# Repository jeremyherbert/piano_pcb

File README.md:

A piano PCB originally designed for use in ENGG2800 at The University of Queensland. Please see `schematic.pdf` for a schematic of the board.

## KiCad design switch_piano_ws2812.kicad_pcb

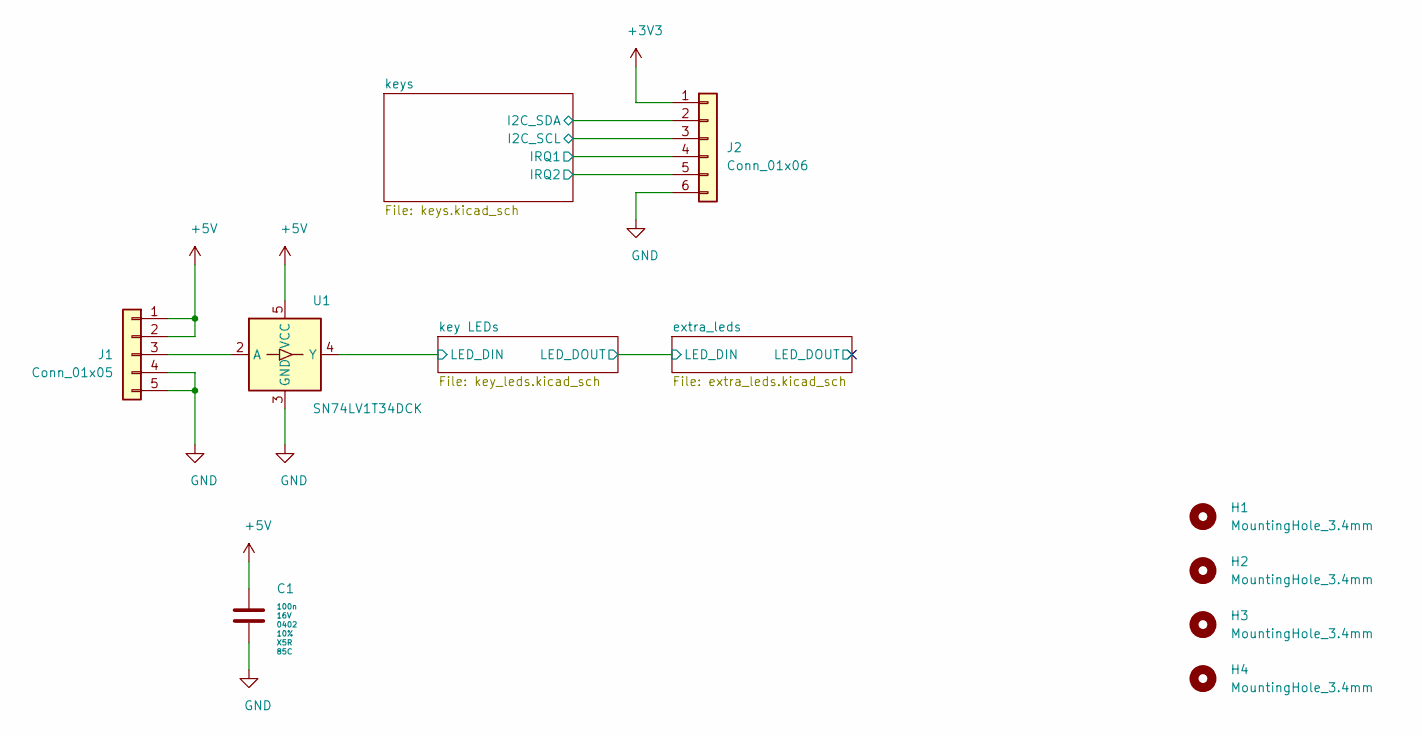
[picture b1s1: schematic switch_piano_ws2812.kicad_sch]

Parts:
C1: C,100n,16V,0402,10%,X5R,85C; C_0402_1005Metric; MFG PN CL05A104KO5NNNC; Digikey 1276-1234-1-ND
H1, H2, H3, H4: MountingHole_3.4mm
J1: Conn_01x05; Molex_KK-254_AE-6410-05A_1x05_P2.54mm_Vertical
J2: Conn_01x06; Molex_KK-254_AE-6410-06A_1x06_P2.54mm_Vertical
U1: SN74LV1T34DCK; SOT-353_SC-70-5

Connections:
+3V3: J2.1; also elsewhere on the board
+5V: C1.1, J1.1, J1.2, U1.5 (VCC); also elsewhere on the board
/I2C_SCL: J2.3; also elsewhere on the board
/IRQ1: J2.4; also elsewhere on the board
/IRQ2: J2.5; also elsewhere on the board
/LED_DIN: U1.4 (Y); also elsewhere on the board
/keys/I2C_SDA_1: J2.2; also elsewhere on the board
unnamed: J1.3, U1.2 (A)

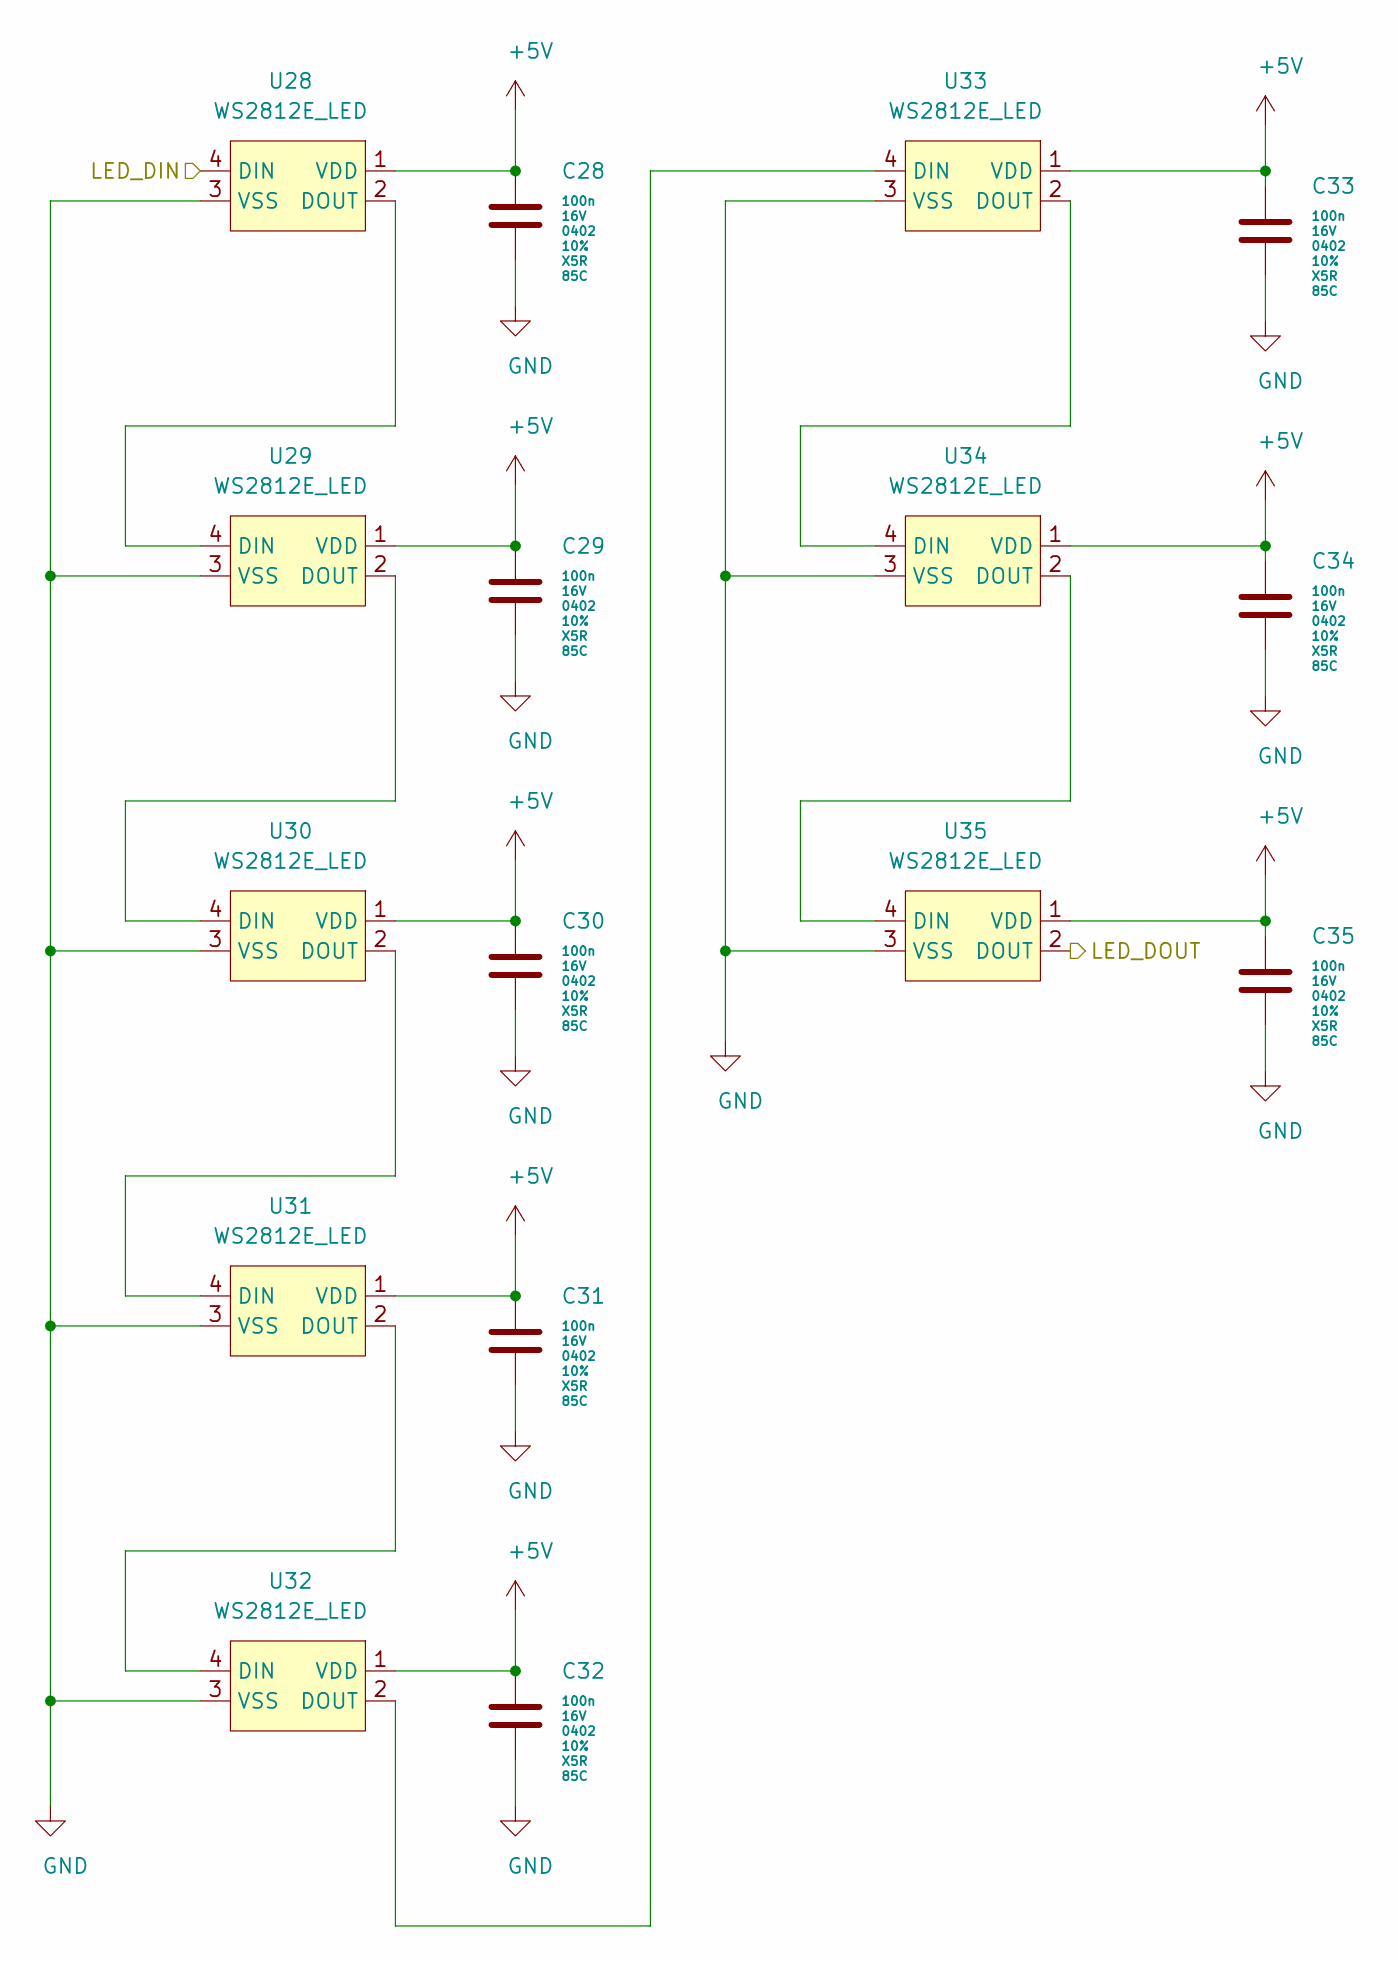
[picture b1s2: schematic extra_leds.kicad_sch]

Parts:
C28, C29, C30, C31, C32, C33, C34, C35: C,100n,16V,0402,10%,X5R,85C; C_0402_1005Metric; MFG PN CL05A104KO5NNNC; Digikey 1276-1234-1-ND
U28, U29, U30, U31, U32, U33, U34, U35: WS2812E_LED; LED_WS2812B_PLCC4_5.0x5.0mm_P3.2mm; MFG PN WS2812E; LCSC C139127

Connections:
+5V: C28.2, C29.2, C30.2, C31.2, C32.2, C33.2, C34.2, C35.2, U28.1 (VDD), U29.1 (VDD), U30.1 (VDD), U31.1 (VDD), U32.1 (VDD), U33.1 (VDD), U34.1 (VDD), U35.1 (VDD); also elsewhere on the board
/LED_DOUT: U35.2 (DOUT)
/LED_DOUT_1: U28.4 (DIN); also elsewhere on the board
unnamed: U28.2 (DOUT), U29.4 (DIN)
unnamed: U29.2 (DOUT), U30.4 (DIN)
unnamed: U30.2 (DOUT), U31.4 (DIN)
unnamed: U31.2 (DOUT), U32.4 (DIN)
unnamed: U32.2 (DOUT), U33.4 (DIN)
unnamed: U33.2 (DOUT), U34.4 (DIN)
unnamed: U34.2 (DOUT), U35.4 (DIN)

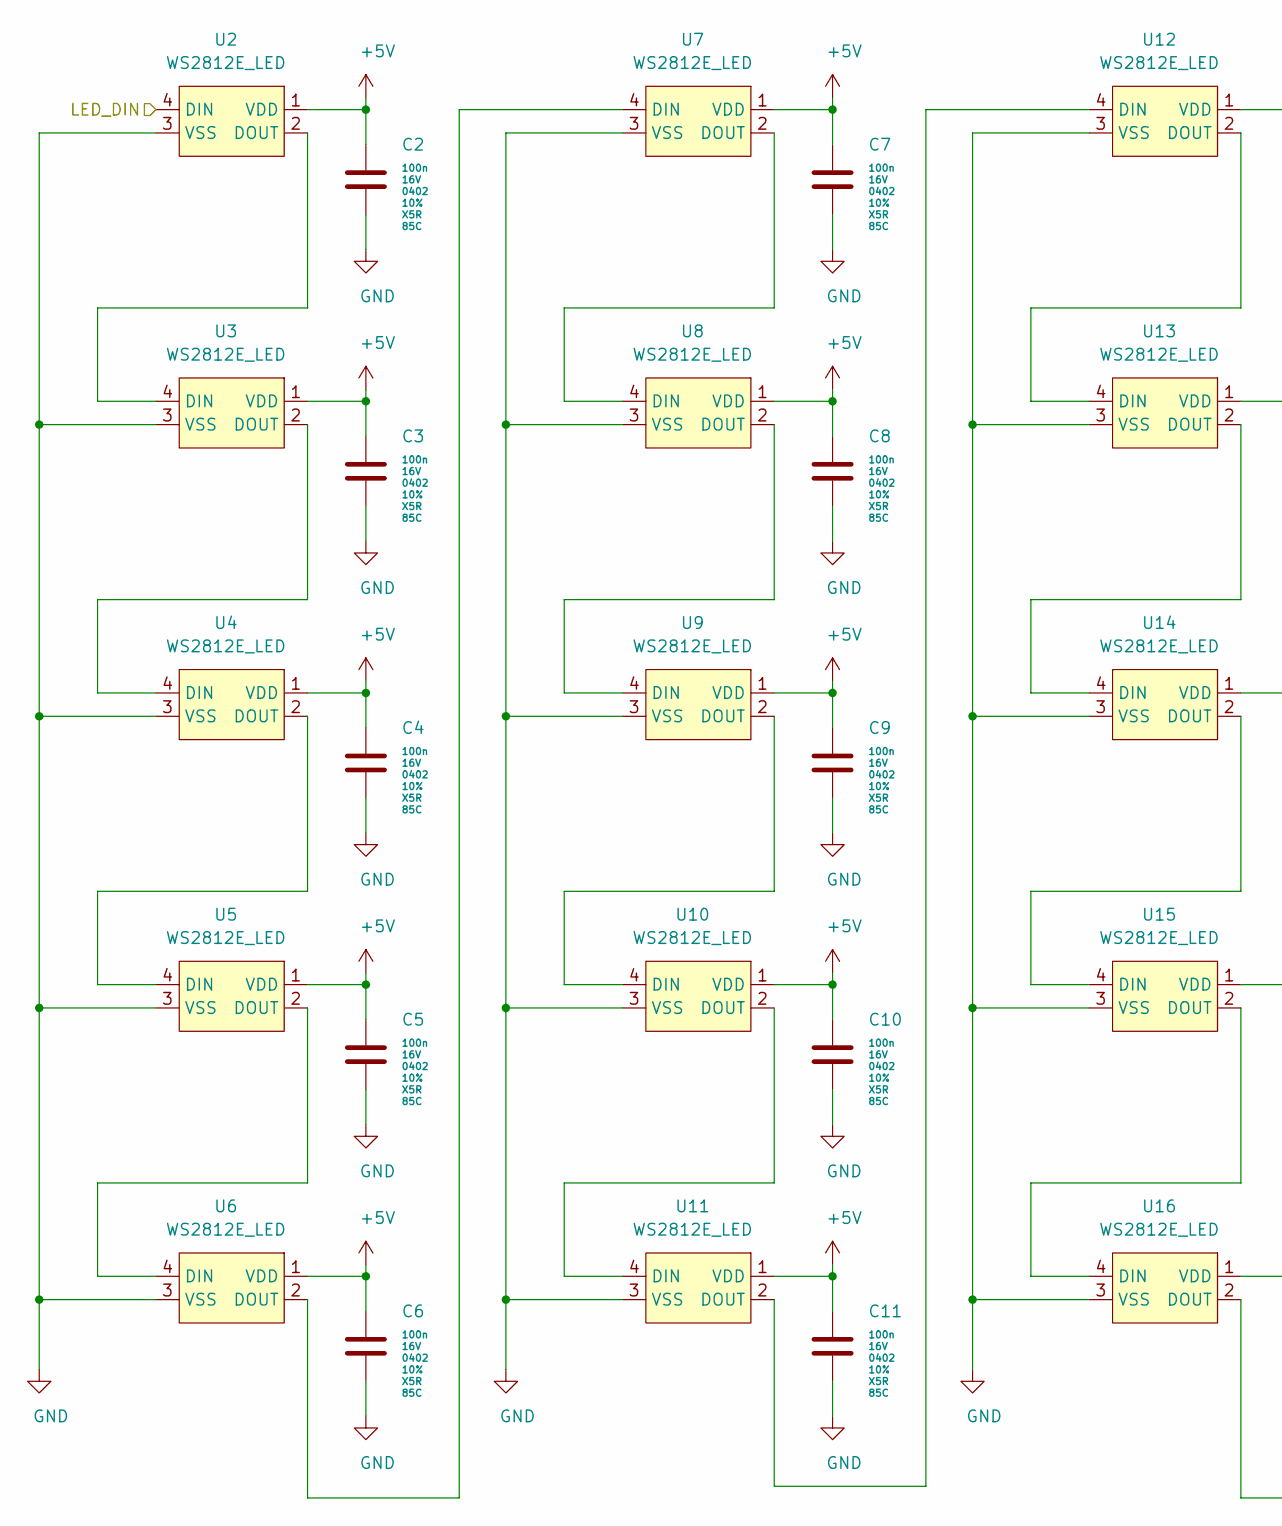
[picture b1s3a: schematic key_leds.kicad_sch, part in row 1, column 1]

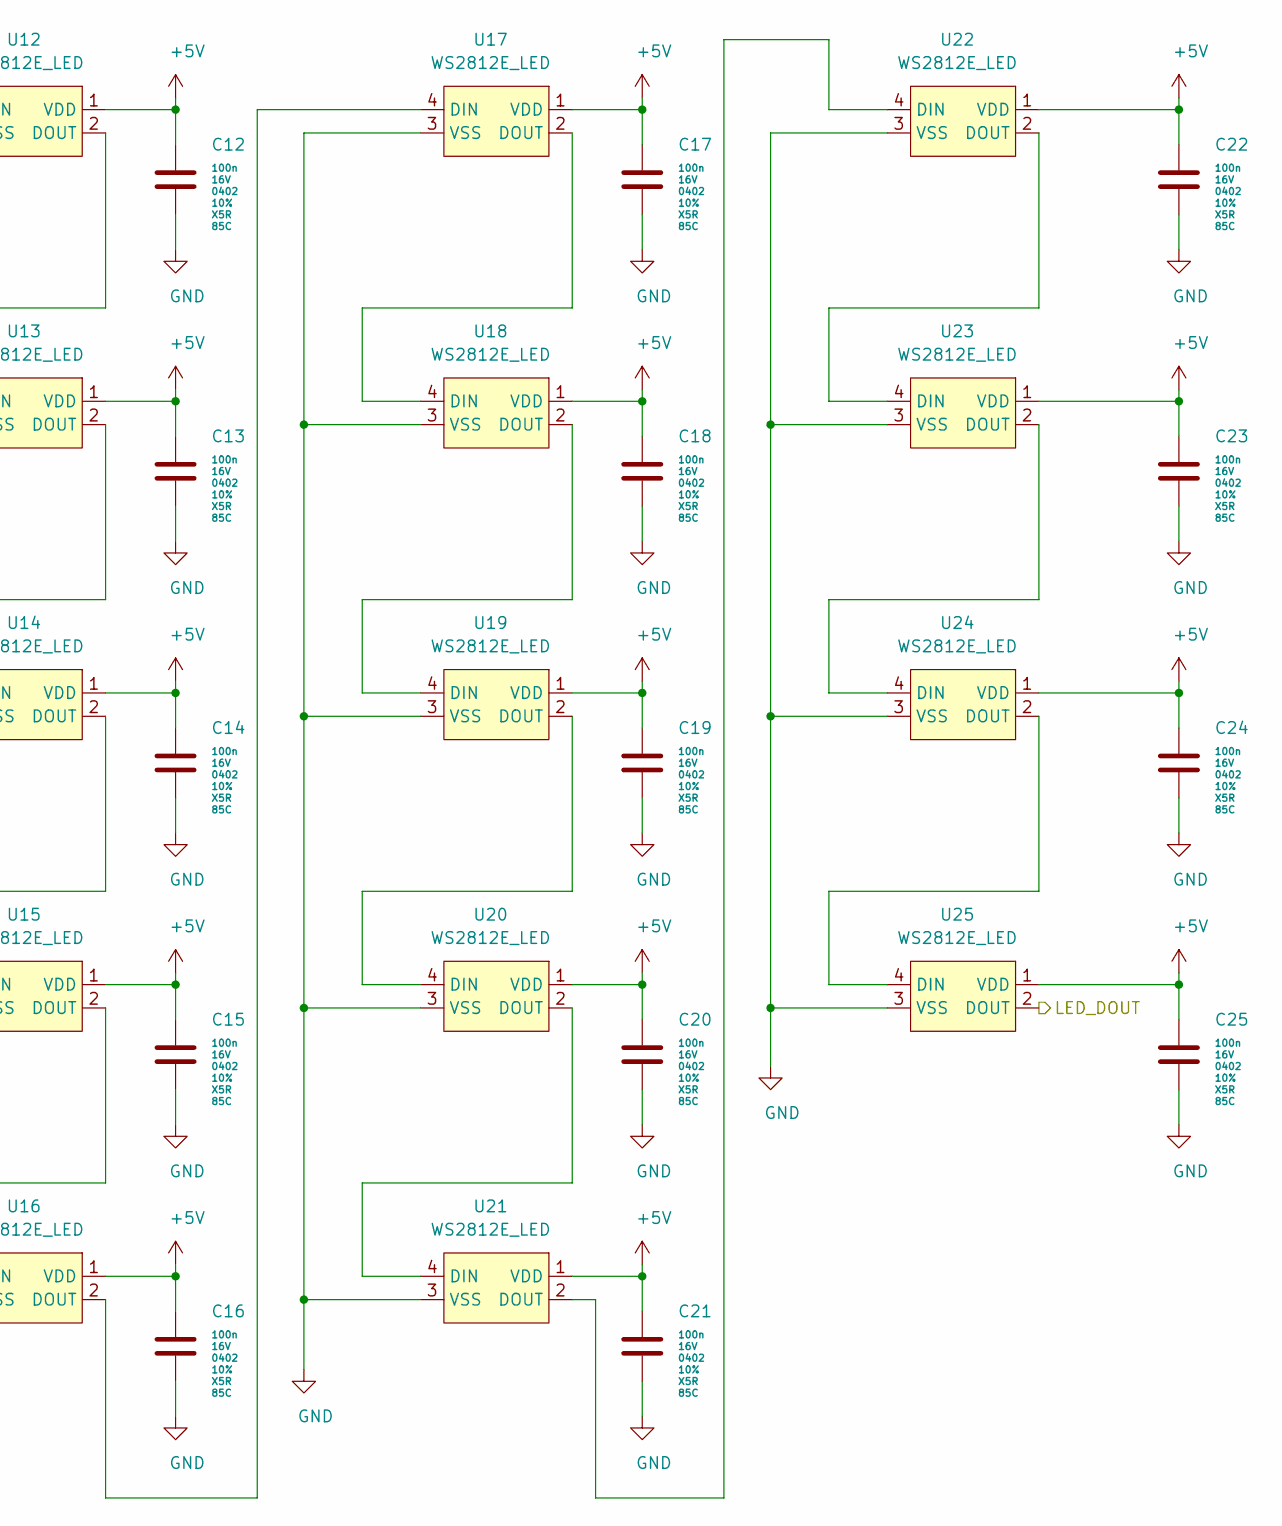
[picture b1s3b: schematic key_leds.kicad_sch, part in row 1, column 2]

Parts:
C2, C3, C4, C5, C6, C7, C8, C9, C10, C11, C12, C13, C14, C15, C16, C17, C18, C19, C20, C21, C22, C23, C24, C25: C,100n,16V,0402,10%,X5R,85C; C_0402_1005Metric; MFG PN CL05A104KO5NNNC; Digikey 1276-1234-1-ND
U2, U3, U4, U5, U6, U7, U8, U9, U10, U11, U12, U13, U14, U15, U16, U17, U18, U19, U20, U21, U22, U23, U24, U25: WS2812E_LED; LED_WS2812B_PLCC4_5.0x5.0mm_P3.2mm; MFG PN WS2812E; LCSC C139127

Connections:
+5V: C2.2, C3.2, C4.2, C5.2, C6.2, C7.2, C8.2, C9.2, C10.2, C11.2, C12.2, C13.2, C14.2, C15.2, C16.2, C17.2, C18.2, C19.2, C20.2, C21.2, C22.2, C23.2, C24.2, C25.2, U2.1 (VDD), U3.1 (VDD), U4.1 (VDD), U5.1 (VDD), U6.1 (VDD), U7.1 (VDD), U8.1 (VDD), U9.1 (VDD), U10.1 (VDD), U11.1 (VDD), U12.1 (VDD), U13.1 (VDD), U14.1 (VDD), U15.1 (VDD), U16.1 (VDD), U17.1 (VDD), U18.1 (VDD), U19.1 (VDD), U20.1 (VDD), U21.1 (VDD), U22.1 (VDD), U23.1 (VDD), U24.1 (VDD), U25.1 (VDD); also elsewhere on the board
/LED_DIN: U2.4 (DIN); also elsewhere on the board
/LED_DOUT_1: U25.2 (DOUT); also elsewhere on the board
unnamed: U2.2 (DOUT), U3.4 (DIN)
unnamed: U3.2 (DOUT), U4.4 (DIN)
unnamed: U4.2 (DOUT), U5.4 (DIN)
unnamed: U5.2 (DOUT), U6.4 (DIN)
unnamed: U6.2 (DOUT), U7.4 (DIN)
unnamed: U7.2 (DOUT), U8.4 (DIN)
unnamed: U8.2 (DOUT), U9.4 (DIN)
unnamed: U10.2 (DOUT), U11.4 (DIN)
unnamed: U9.2 (DOUT), U10.4 (DIN)
unnamed: U11.2 (DOUT), U12.4 (DIN)
unnamed: U12.2 (DOUT), U13.4 (DIN)
unnamed: U13.2 (DOUT), U14.4 (DIN)
unnamed: U14.2 (DOUT), U15.4 (DIN)
unnamed: U15.2 (DOUT), U16.4 (DIN)
unnamed: U17.2 (DOUT), U18.4 (DIN)
unnamed: U16.2 (DOUT), U17.4 (DIN)
unnamed: U18.2 (DOUT), U19.4 (DIN)
unnamed: U19.2 (DOUT), U20.4 (DIN)
unnamed: U20.2 (DOUT), U21.4 (DIN)
unnamed: U22.2 (DOUT), U23.4 (DIN)
unnamed: U21.2 (DOUT), U22.4 (DIN)
unnamed: U23.2 (DOUT), U24.4 (DIN)
unnamed: U24.2 (DOUT), U25.4 (DIN)

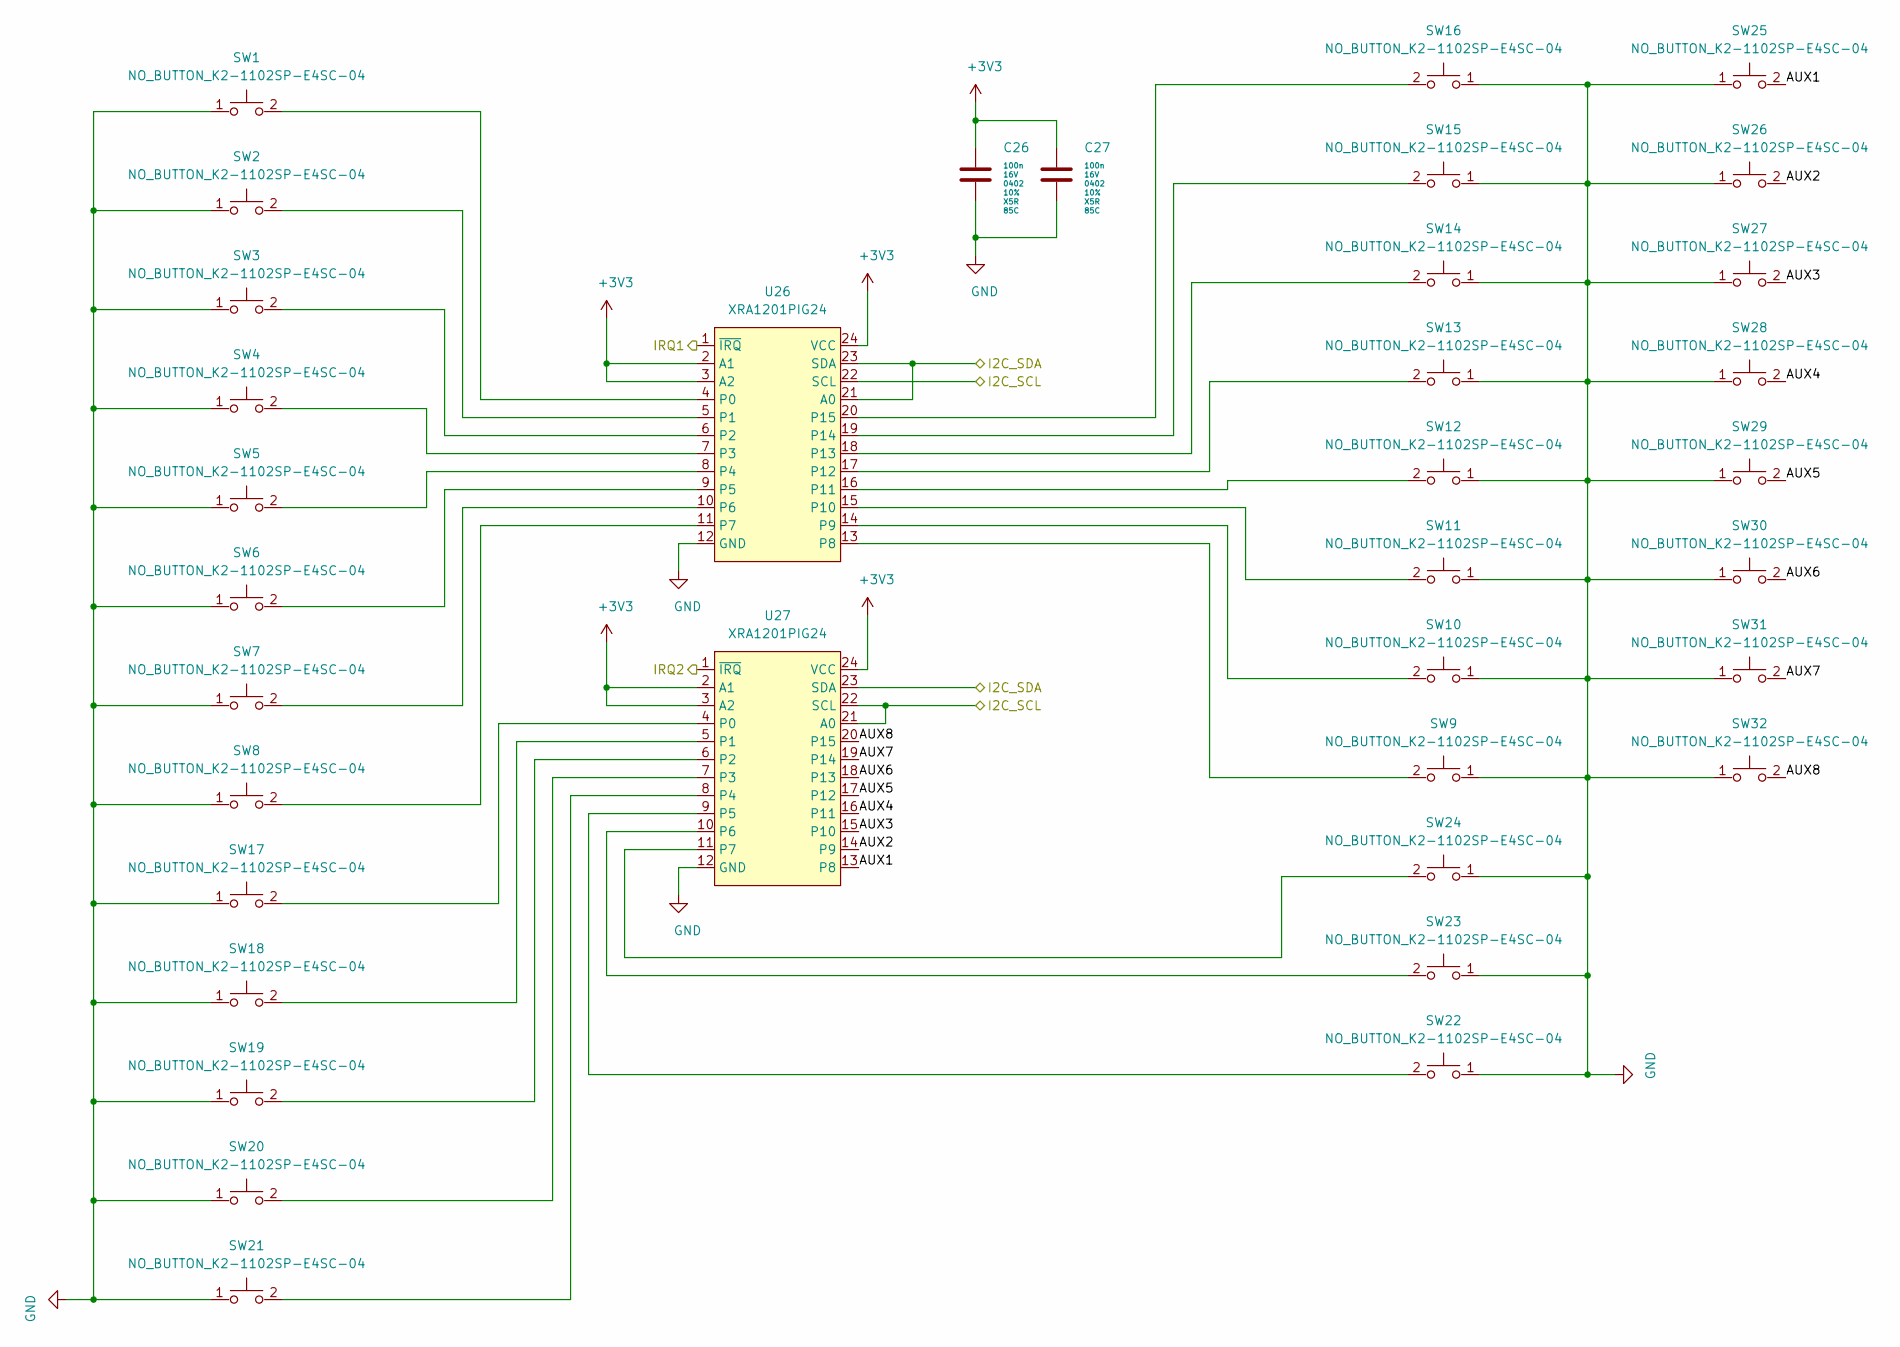
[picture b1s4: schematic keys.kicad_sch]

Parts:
C26, C27: C,100n,16V,0402,10%,X5R,85C; C_0402_1005Metric; MFG PN CL05A104KO5NNNC; Digikey 1276-1234-1-ND
SW1, SW2, SW3, SW4, SW5, SW6, SW7, SW8, SW9, SW10, SW11, SW12, SW13, SW14, SW15, SW16, SW17, SW18, SW19, SW20, SW21, SW22, SW23, SW24, SW25, SW26, SW27, SW28, SW29, SW30, SW31, SW32: NO_BUTTON_K2-1102SP-E4SC-04; SW_SPST_PTS645; MFG PN K2-1102SP-E4SC-04; LCSC C136669
U26, U27: XRA1201PIG24; TSSOP-24_4.4x7.8mm_P0.65mm; MFG PN XRA1201PIG24; Digikey XRA1201PIG24TR-F-ND

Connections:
+3V3: C26.1, C27.1, U26.2 (A1), U26.3 (A2), U26.24 (VCC), U27.2 (A1), U27.3 (A2), U27.24 (VCC); also elsewhere on the board
/I2C_SCL: U26.22 (SCL), U27.21 (A0), U27.22 (SCL); also elsewhere on the board
/IRQ1: U26.1 (~IRQ); also elsewhere on the board
/IRQ2: U27.1 (~IRQ); also elsewhere on the board
/keys/AUX1: SW25.2 (A), U27.13 (P8)
/keys/AUX2: SW26.2 (A), U27.14 (P9)
/keys/AUX3: SW27.2 (A), U27.15 (P10)
/keys/AUX4: SW28.2 (A), U27.16 (P11)
/keys/AUX5: SW29.2 (A), U27.17 (P12)
/keys/AUX6: SW30.2 (A), U27.18 (P13)
/keys/AUX7: SW31.2 (A), U27.19 (P14)
/keys/AUX8: SW32.2 (A), U27.20 (P15)
/keys/I2C_SDA_1: U26.21 (A0), U26.23 (SDA), U27.23 (SDA); also elsewhere on the board
unnamed: SW1.2 (A), U26.4 (P0)
unnamed: SW2.2 (A), U26.5 (P1)
unnamed: SW3.2 (A), U26.6 (P2)
unnamed: SW4.2 (A), U26.7 (P3)
unnamed: SW5.2 (A), U26.8 (P4)
unnamed: SW6.2 (A), U26.9 (P5)
unnamed: SW7.2 (A), U26.10 (P6)
unnamed: SW8.2 (A), U26.11 (P7)
unnamed: SW9.2 (A), U26.13 (P8)
unnamed: SW10.2 (A), U26.14 (P9)
unnamed: SW11.2 (A), U26.15 (P10)
unnamed: SW12.2 (A), U26.16 (P11)
unnamed: SW13.2 (A), U26.17 (P12)
unnamed: SW17.2 (A), U27.4 (P0)
unnamed: SW18.2 (A), U27.5 (P1)
unnamed: SW19.2 (A), U27.6 (P2)
unnamed: SW20.2 (A), U27.7 (P3)
unnamed: SW21.2 (A), U27.8 (P4)
unnamed: SW22.2 (A), U27.9 (P5)
unnamed: SW23.2 (A), U27.10 (P6)
unnamed: SW24.2 (A), U27.11 (P7)
unnamed: SW14.2 (A), U26.18 (P13)
unnamed: SW15.2 (A), U26.19 (P14)
unnamed: SW16.2 (A), U26.20 (P15)

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
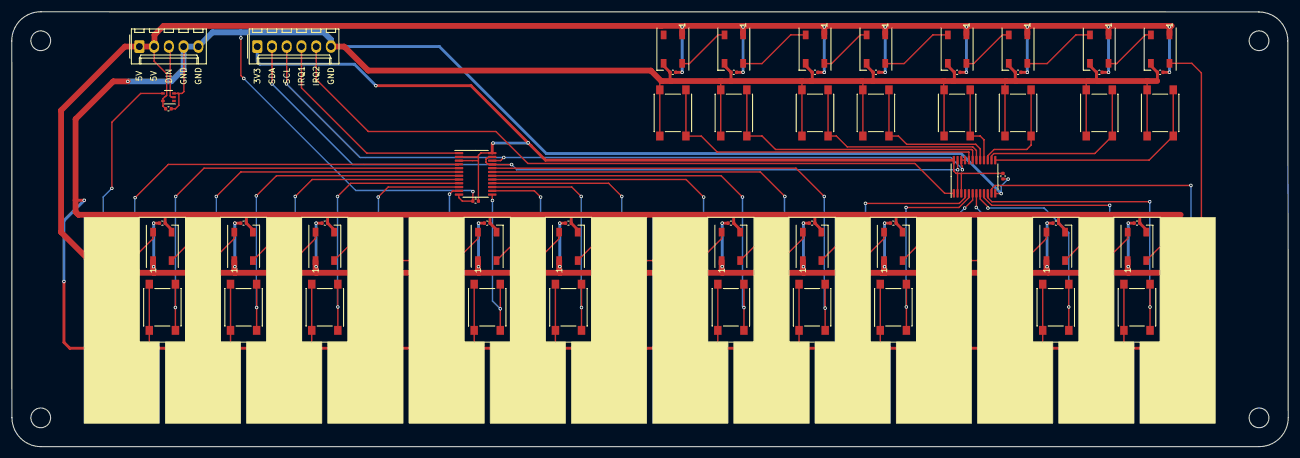
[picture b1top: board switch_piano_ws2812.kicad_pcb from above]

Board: 2 copper layers, 220.0 x 75.0 mm, 108 parts (0 on the bottom side), 72 nets.

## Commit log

2021-03-01 Initial public release
2021-03-01 add license and readme
